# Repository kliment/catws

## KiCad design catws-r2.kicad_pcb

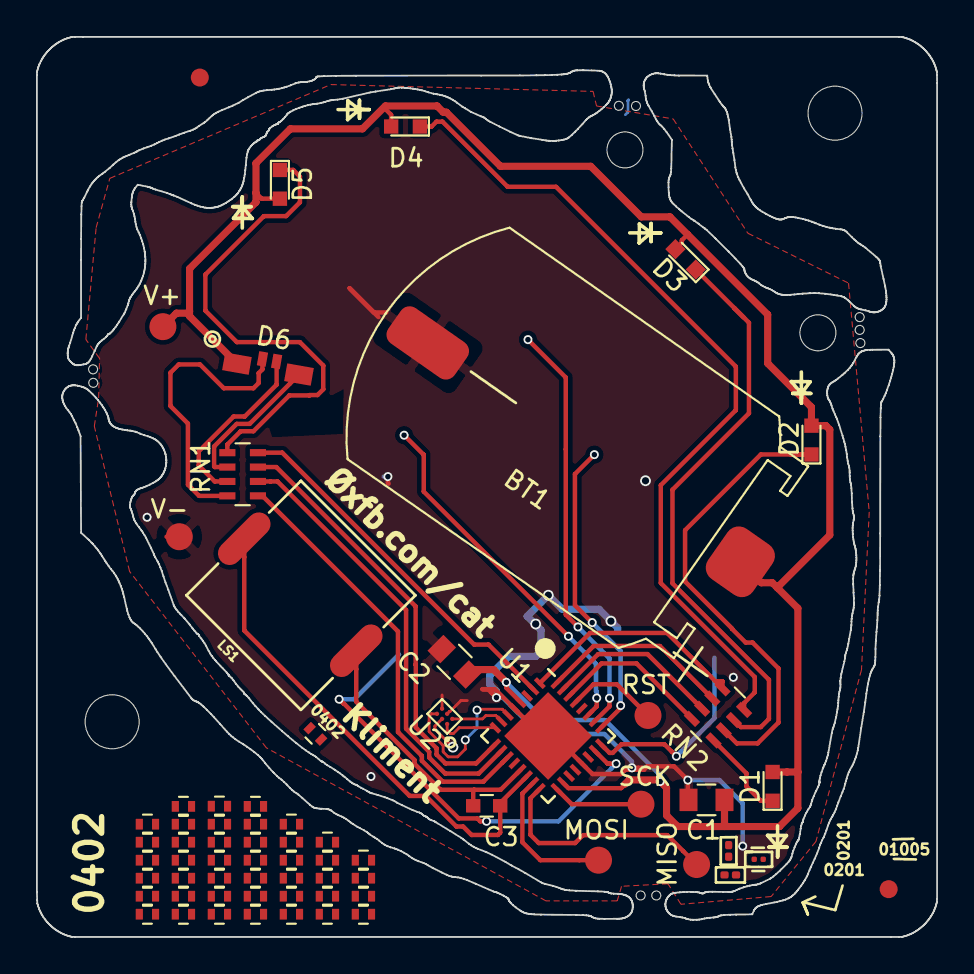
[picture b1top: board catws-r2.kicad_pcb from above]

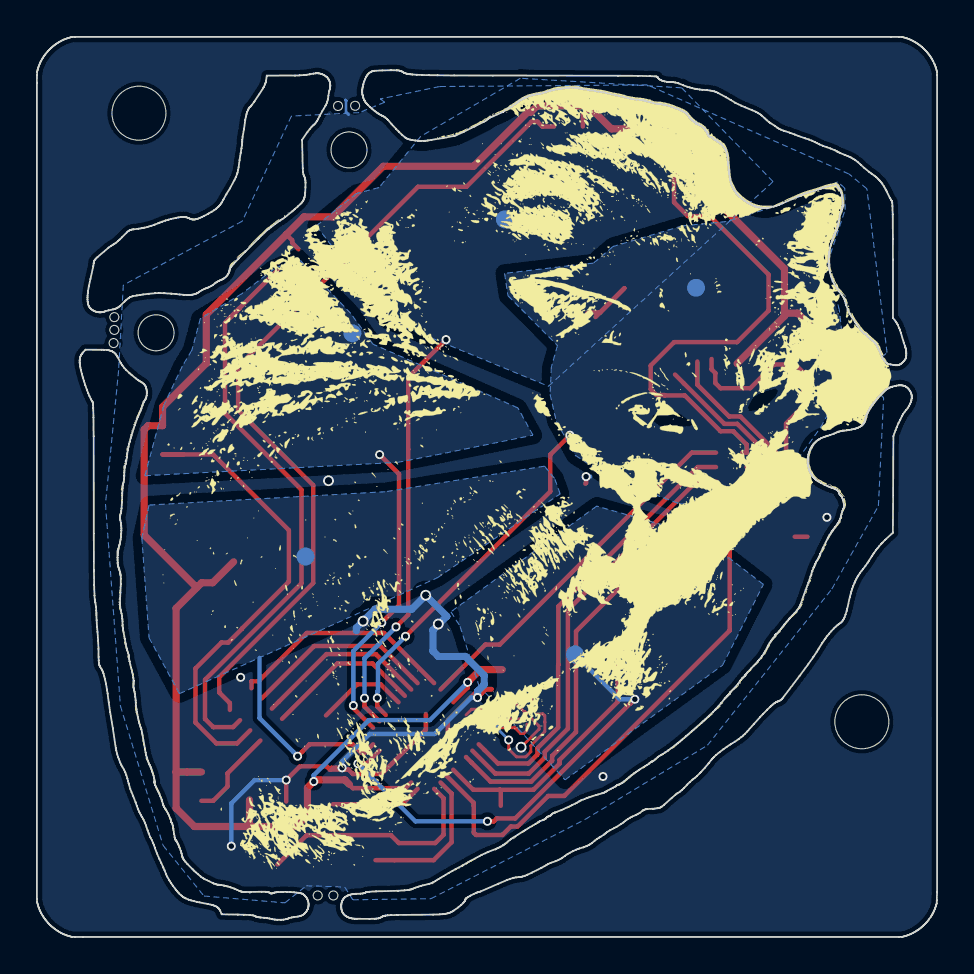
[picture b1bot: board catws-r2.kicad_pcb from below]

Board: 2 copper layers, 50.0 x 50.0 mm, 26 parts (5 on the bottom side), 32 nets.

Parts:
BT1: Battery_Cell; KLS5-CR2032-11
C1, C2: C; C_0805
C3: C; C_0603
D1, D2, D3, D4, D5: LED; LED_0603
D6: LED_ARGB; HQ12-2353RBGC
J1, J2, J3, J4, J5: TEST_1P; Measurement_Point_Round-SMD-Pad_Big
LS1: Speaker_Crystal; Murata-PKMCS
MISO: TEST_1P; Measurement_Point_Round-SMD-Pad_Small
MOSI: TEST_1P; Measurement_Point_Round-SMD-Pad_Small
RN1, RN2: R_Pack04; R_Array_Concave_4x0603
RST: TEST_1P; Measurement_Point_Round-SMD-Pad_Small
SCK: TEST_1P; Measurement_Point_Round-SMD-Pad_Small
U1: ATTINY88-MU; QFN-32-1EP_5x5mm_Pitch0.5mm
U2: BRCC064GWZ-3; WLCSP-6_1.4x1.0mm_P0.4mm
V+: TEST_1P; Measurement_Point_Round-SMD-Pad_Small
V-: TEST_1P; Measurement_Point_Round-SMD-Pad_Small

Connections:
/T0: J1.1, U1.23
/T1: J2.1, U1.24
/T2: J3.1, U1.25
/T3: J4.1, U1.26
/T4: J5.1, U1.27
GND: BT1.2, C1.2, C2.2, U1.5, U1.21, U2.A2, U2.B2, U2.B3, V-.1
unnamed: BT1.1, C1.1, C2.1, D1.2, D2.2, D3.2, D4.2, D5.2, D6.1, U1.4, U1.18, V+.1
unnamed: C3.1, LS1.1, U1.13
unnamed: C3.2, LS1.2, U1.14
unnamed: D1.1, RN2.1
unnamed: D2.1, RN2.2
unnamed: D3.1, RN2.3
unnamed: D4.1, RN2.4
unnamed: D5.1, RN1.5
unnamed: D6.2, RN1.6
unnamed: D6.3, RN1.7
unnamed: D6.4, RN1.8
unnamed: MISO.1, U1.16
unnamed: MOSI.1, U1.15
unnamed: RST.1, U1.29
unnamed: RN1.1, U1.11
unnamed: RN1.2, U1.10
unnamed: RN1.3, U1.9
unnamed: RN1.4, U1.2
unnamed: RN2.5, U1.1
unnamed: RN2.6, U1.32
unnamed: RN2.7, U1.31
unnamed: RN2.8, U1.30
unnamed: SCK.1, U1.17
unnamed: U1.6, U2.A3
unnamed: U1.7, U2.B1
unnamed: U1.8, U2.A1

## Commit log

2019-01-31 Initial synthesis tests
2019-02-01 Use python3 explicitly
2019-02-07 Test audio output
2019-02-10 Implement low power sleep mode Add horrible hiss and horrible loud purr Add broken time-based measurement mode
2019-02-10 Add visual effects
2019-02-10 Try increasing purr volume
2019-02-10 Add purry/hissy pseudo-state-machine Implement LFHR (linear feedback hiss register)
2019-02-10 Cleanup, volume changes without clicks, and disable the ISR when volume = 0 or sleep mode enabled
2019-02-10 Fix hiss
2019-02-10 Silence comes before a hiss
2019-02-10 Sort enum, move sleep things to separate function
2019-02-10 Rename sleep_mode to sleep()
2019-02-10 Refactor state machine some more
2019-02-10 Fix mode setting
2019-02-10 fix crash
2019-02-10 Remove binaries
2019-02-10 Fix overstim
2019-02-10 Fix overstim some more
2019-02-10 Plateau happiness before overstim
2019-02-10 Remove more binaries
2019-02-10 Hiss when going against the grain moves happiness below the loop limit
2019-02-10 Fade out purring when going to sleep
2019-02-10 Fade breathing
2019-02-10 Reduce purr duration after petting has stopped.
2019-02-10 Fix hissing, again
2019-02-10 Add parens
2019-02-19 Revert "Reduce purr duration after petting has stopped."
    This reverts commit 9a0ce220ef02b9019fc9a824d8e155b2acef64fa.
2019-04-13 second revision layout and schema differential drive for piezo add cap in parallel with piezo add tricky footprints (0201, 01005, µBGA2x3)
2019-12-14 Add missing library cache files and minor changes to firmware sensitivity thresholds
2022-08-27 Add manual PDF and latest revision of PCB (for 2022 workshops)
2022-08-27 Move waveform to progmem to fit on attiny48
